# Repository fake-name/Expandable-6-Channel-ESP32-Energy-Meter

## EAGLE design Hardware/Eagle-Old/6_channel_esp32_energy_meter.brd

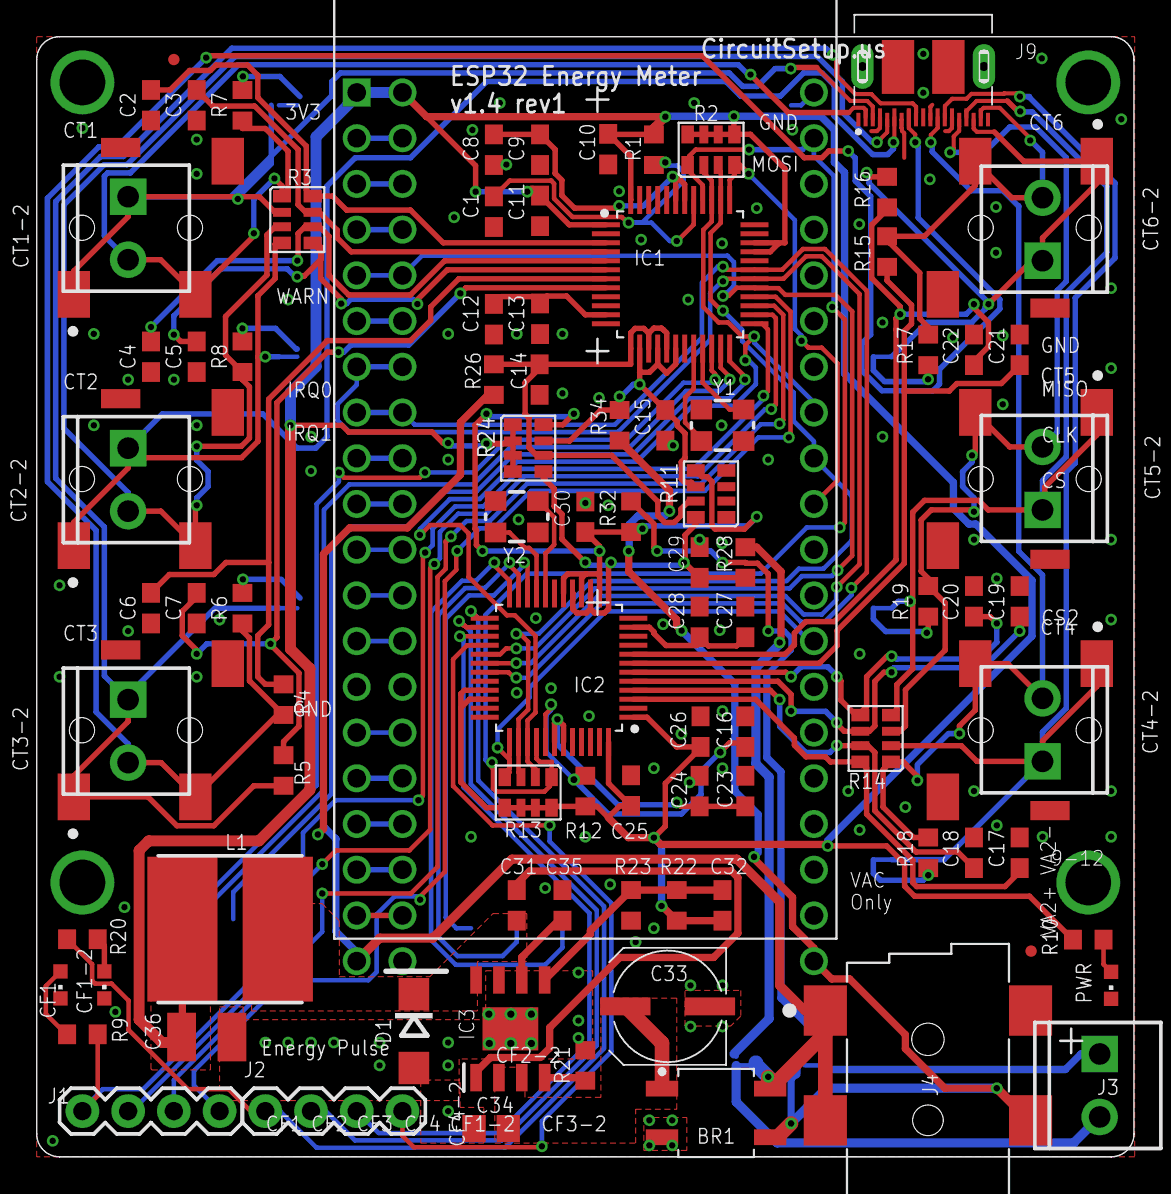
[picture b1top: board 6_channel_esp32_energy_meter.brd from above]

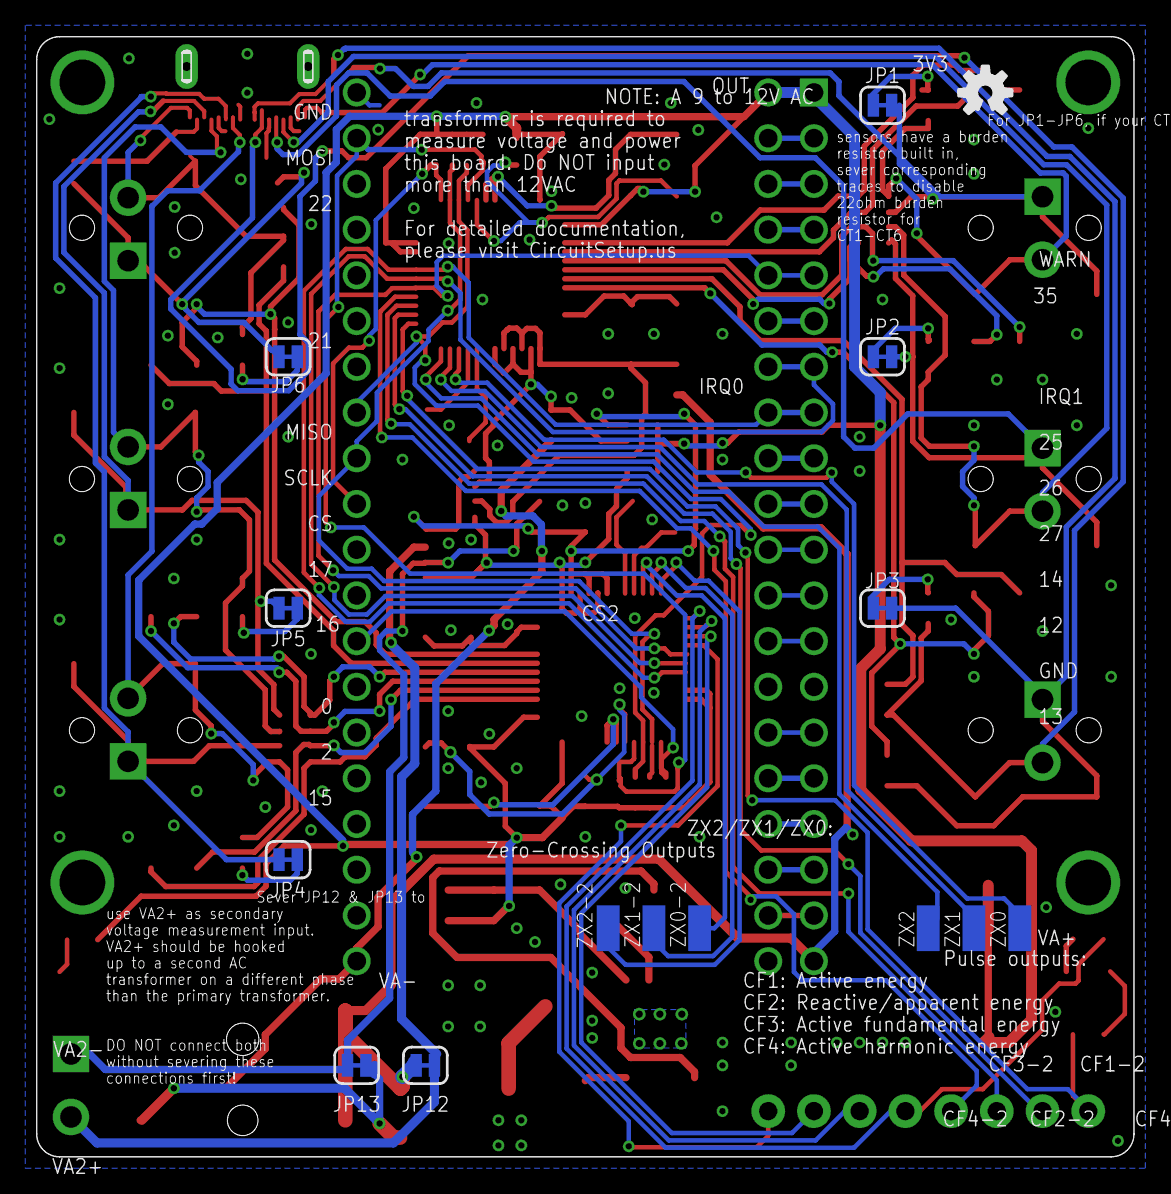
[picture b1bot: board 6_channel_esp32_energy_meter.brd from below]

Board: 2 copper layers, 61.0 x 62.2 mm, 114 parts (15 on the bottom side), 95 nets.

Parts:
BR1: 50V/2A; SOP270P700X270-4
C1, C9, C10, C11, C13, C16, C24, C25, C26, C28, C31: 0.1uF; C0603
C2, C3, C4, C5, C6, C7, C17, C18, C19, C20, C21, C22: .33uF; C0603
C8, C12, C23, C27: 10uF; C0603
C14, C15, C29, C30: 18nF; C0603
C32: 220pF; C0603
C33: 100uF/25V; UD-6,3X7,7_NICHICON
C34: 10uF/25V; C0805
C35: 10nF; C0603
C36: 100uF/6.3V/1210; C1210
CF1, CF1-2: BLU; CHIPLED_0603
CT1, CT2, CT3, CT4, CT5, CT6: SCREWTERMINAL-3.5MM-2
CT1-2, CT2-2, CT3-2, CT4-2, CT5-2, CT6-2: SJ2-35813B-SMT-TR; CUI_SJ2-35813B-SMT-TR
D1: DO214AC
FD1, FD2: FIDUCIALUFIDUCIAL; FIDUCIAL-MICRO
IC1, IC2: ATM90E32AS; QFP50P900X900X120-48
IC3: LMR14020SDDA; SOIC127P600X170-9N
J1, J2: 1X04
J3: SCREWTERMINAL-3.5MM-2
J4: 9-12VAC; CUI_PJ-002AH-SMT-TR
J5, J6, J8: PINHD1X1-SM1X01_SM; 1X01-SM
J9: PKS019-4011-0; PKS01940110
J16: PINHD-1X19; 1X19
JP1, JP2, JP3, JP4, JP5, JP6, JP12, JP13: SMT-JUMPER_2_NC_TRACE_SILK
L1: 3.3uH / 8x8mm; INDPM8082X300N
LOGO1: OSHW-LOGOS; OSHW-LOGO-S
PWR: GRN; CHIPLED_0603
R1, R12: 10K; R0603
R2, R13: 10K; RA1206-8
R3, R14: 100; RA1206-8
R4, R5, R15, R16: 100; R0603
R6, R7, R8, R17, R18, R19: 22; R0603
R9, R10, R20: 1k; R0603
R11: 1K; RA1206-8
R21: 20k; R0603
R22: 34k; R0603
R23: 10k; R0603
R24: 20K; RA1206-8
R26, R28, R32, R34: 20k 1/4W; R0603
U1: ESP32-DEVKITC-32D; MODULE_ESP32-DEVKITC-32D
Y1, Y2: 16.384MHz; CRYSTAL-SMD-3.2X2.5MM
ZX0, ZX0-2, ZX1, ZX1-2, ZX2, ZX2-2: WIREPADSMD1,27-254; SMD1,27-2,54

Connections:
!CS: IC1.37, R2.4, U1.29
!CS-2: IC2.37, R13.4, U1.32
!RESET: C1.2, IC1.41, R1.2
!RESET2: C16.2, IC2.41, R12.2
BOOT: C31.1, IC3.1
CF1: IC1.25, J1.4, R9.2
CF1-2: IC2.25, J2.4, R20.2
CF2: IC1.26, J1.3
CF2-2: IC2.26, J2.3
CF3: IC1.27, J1.2
CF3-2: IC2.27, J2.2
CF4: IC1.28, J1.1
CF4-2: IC2.28, J2.1
FB: C32.2, IC3.5, R22.1, R23.2
GND: BR1.2, C1.1, C2.2, C3.1, C4.2, C5.1, C6.2, C7.1, C8.1, C9.1, C10.1, C11.1, C12.2, C13.2, C14.2, C15.2, C16.1, C17.2, C18.1, C19.2, C20.1, C21.2, C22.1, C23.1, C24.1, C25.1, C26.1, C27.2, C28.2, C29.2, C30.2, C33.-, C34.2, C35.2, C36.2, CF1.C, CF1-2.C, D1.A, IC1.2, IC1.12, IC1.19, IC1.32, IC1.36, IC1.44, IC1.47, IC2.2, IC2.12, IC2.19, IC2.32, IC2.36, IC2.44, IC2.47, IC3.7, IC3.9, J9.1, J9.4, J9.7, J9.10, J9.11, J9.14, J9.19, J9.21, J9.22, J9.P$1, J9.P$2, J16.14, PWR.C, R11.1, R11.2, R11.3, R11.4, R21.1, R23.1, U1.14, U1.20, U1.26, Y1.2, Y1.4, Y2.2, Y2.4
IA+: CT1.2, CT1-2.2, J9.2, R3.1, R7.2
IA+-2: CT4.2, CT4-2.2, J9.12, R14.1, R18.2
IA-: CT1.1, CT1-2.1, J9.3, JP1.2, R3.2
IA--2: CT4.1, CT4-2.1, J9.13, JP4.2, R14.2
IAN: C3.2, IC1.4, R3.7
IAN-2: C18.2, IC2.4, R14.7
IAP: C2.1, IC1.3, R3.8
IAP-2: C17.1, IC2.3, R14.8
IB+: CT2.2, CT2-2.2, J9.5, R3.3, R8.2
IB+-2: CT5.2, CT5-2.2, J9.15, R14.3, R19.2
IB-: CT2.1, CT2-2.1, J9.6, JP2.2, R3.4
IB--2: CT5.1, CT5-2.1, J9.16, JP5.2, R14.4
IBN: C5.2, IC1.6, R3.5
IBN-2: C20.2, IC2.6, R14.5
IBP: C4.1, IC1.5, R3.6
IBP-2: C19.1, IC2.5, R14.6
IC+: CT3.2, CT3-2.2, J9.8, R4.2, R6.2
IC+-2: CT6.2, CT6-2.2, J9.18, R15.2, R17.2
IC-: CT3.1, CT3-2.1, J9.9, JP3.2, R5.2
IC--2: CT6.1, CT6-2.1, J9.17, JP6.2, R16.2
ICN: C7.2, IC1.8, R5.1
ICN-2: C22.2, IC2.8, R16.1
ICP: C6.1, IC1.7, R4.1
ICP-2: C21.1, IC2.7, R15.1
IO12: J16.13, U1.13
IO13: J16.15, U1.15
IO14: J16.12, U1.12
IO25: J16.9, U1.9
IO26: J16.10, U1.10
IO27: J16.11, U1.11
IO35: J16.6, U1.6
IRQ0: IC1.30, IC2.30, J16.7, U1.7
IRQ1: IC1.31, IC2.31, J16.8, U1.8
MISO: IC1.39, IC2.39, R2.2, R13.2, U1.27
MOSI: IC1.40, IC2.40, R2.1, R13.1, U1.21
unnamed: JP1.1, R7.1
unnamed: JP2.1, R8.1
unnamed: CF1.A, R9.1
unnamed: JP3.1, R6.1
unnamed: JP4.1, R18.1
unnamed: JP5.1, R19.1
unnamed: JP6.1, R17.1
unnamed: J16.2, U1.2
unnamed: J16.3, U1.3
unnamed: PWR.A, R10.1
unnamed: CF1-2.A, R20.1
unnamed: J16.4, U1.4
unnamed: J16.16, U1.16
unnamed: J16.17, U1.17
unnamed: J16.18, U1.18
unnamed: J16.19, U1.19
OSCI: IC1.20, Y1.1
OSCI2: IC2.20, Y2.1
OSCO: IC1.21, Y1.3
OSCO2: IC2.21, Y2.3
RT: IC3.4, R21.2
SCLK: IC1.38, IC2.38, R2.3, R13.3, U1.28
SS: C35.1, IC3.6
SW: C31.2, D1.C, IC3.8, L1.1
VA2+: J3.2, JP12.1, R28.2
VA2-: J3.1, JP13.1, R32.2
VA+: BR1.4, J4.1A, J4.1B, J8.1, JP12.2, R26.2
VA-: BR1.3, J4.2, J6.1, JP13.2, R34.2
VAN: C15.1, IC1.14, IC1.16, IC1.18, R11.6, R24.7, R34.1
VAN2: C30.1, IC2.14, IC2.16, IC2.18, R11.5, R24.8, R32.1
VAP: C14.1, IC1.13, IC1.15, IC1.17, R11.7, R24.6, R26.1
VAP2: C29.1, IC2.13, IC2.15, IC2.17, R11.8, R24.5, R28.1
VDD: C10.2, C11.2, C25.2, C26.2, C32.1, C36.1, IC1.1, IC1.33, IC1.34, IC1.48, IC2.1, IC2.33, IC2.34, IC2.48, J16.1, L1.2, R1.1, R2.5, R2.6, R2.7, R2.8, R10.2, R12.1, R13.5, R13.6, R13.7, R13.8, R22.2, R24.1, R24.2, R24.3, R24.4, U1.1
VDD2: C23.2, C24.2, IC2.42, IC2.43
VDD18: C8.2, C9.2, IC1.42, IC1.43
VIN: BR1.1, C33.+, C34.1, IC3.2, IC3.3
VREF: C12.1, C13.1, IC1.11
VREF2: C27.1, C28.1, IC2.11
WARN: IC1.29, IC2.29, J16.5, U1.5
ZX0: IC1.22, ZX0.1
ZX0-2: IC2.22, ZX0-2.1
ZX1: IC1.23, ZX1.1
ZX1-2: IC2.23, ZX1-2.1
ZX2: IC1.24, ZX2.1
ZX2-2: IC2.24, ZX2-2.1

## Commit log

2020-08-23 Convert to kicad.
2020-08-23 Make the schematic not terrible.
2020-08-23 Working on layout.
2020-08-24 Minor footprint cleanup.
2020-08-24 Project cleanup. Kicad has too many garbage files it sprays everywhere.
2020-08-25 Transformer PCB.
2020-08-25 Interface board.
2020-08-26 This seems to be getting progressively more complicated. Library cleanup, moved everything to my system library.
2020-08-29 Updates! I keep adding features.
2020-08-30 Progress!
2020-08-30 Bus-based board variant.
2020-08-31 Common-bus variant of the power monitor.
2020-08-31 MOAR.
2020-09-04 Blerp.
2020-09-06 Switch to a better jack.

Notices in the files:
parts and their libraries:
SparkFun-Connectors: Licensing: Creative Commons ShareAlike 4.0 International - https://creativecommons.org/licenses/by-sa/4.0
